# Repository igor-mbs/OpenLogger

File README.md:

# OpenLogger

<!--

"Halley's method"
=640x640
{width=320 height=240}
-->
<!-- <figure>

<figcaption>Halley's method</figcaption>
</figure> -->
<!--  -->
<!--  -->
<!--  -->
<!--  -->
<!--  -->
<!--  -->
<!-- {width=50 height=50} -->
<!-- {width=500px}
{width=50} -->
<!-- {width=50%} -->

## Introduction

&nbsp;&nbsp;&nbsp;&nbsp;This project is and Open-source portable datalogger based on the ATmega328p microcontroller.

&nbsp;&nbsp;&nbsp;&nbsp; The intent for this project is to provide an cost-friendly solution to support micro and small companies as well as the generall public. The project consists in an semi-modular data acquisition device capable of comunication with probes compatible with digital comunication, like I2C, SPI, serial and PWM.
Open-source portable datalogger project based on the ATmega328p microcontroller.

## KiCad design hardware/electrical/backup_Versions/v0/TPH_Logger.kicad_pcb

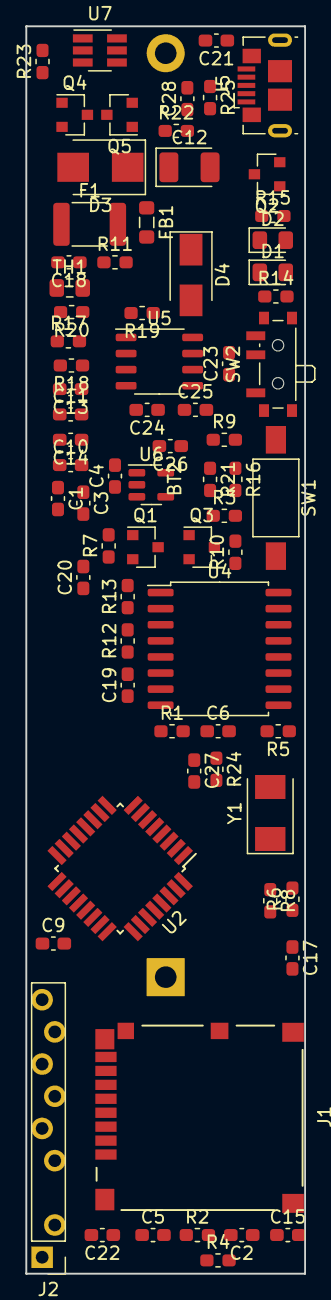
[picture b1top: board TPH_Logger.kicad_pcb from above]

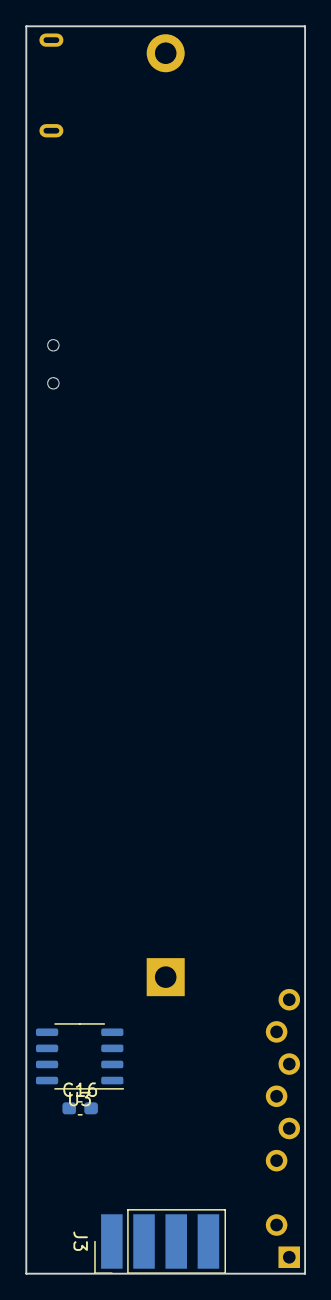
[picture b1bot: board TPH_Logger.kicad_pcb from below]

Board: 2 copper layers, 22.0 x 98.4 mm, 77 parts (3 on the bottom side), 44 nets, no tracks yet.

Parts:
BT2: 18650 Li-Ion (4.3-2.7V); 18650holder
C1, C9, C11, C13, C14, C28: 100n; C_0603_1608Metric_Pad1.08x0.95mm_HandSolder
C2, C3, C4, C5, C17, C18, C19, C20: 12p; C_0603_1608Metric_Pad1.08x0.95mm_HandSolder
C6, C21, C22: 1u; C_0603_1608Metric_Pad1.08x0.95mm_HandSolder
C10, C26: 10n; C_0603_1608Metric_Pad1.08x0.95mm_HandSolder
C12: 4.7u; CP_EIA-3528-21_Kemet-B_Pad1.50x2.35mm_HandSolder
C15, C16: 22p; C_0603_1608Metric_Pad1.08x0.95mm_HandSolder
C23, C27: 4.7u; C_0603_1608Metric_Pad1.08x0.95mm_HandSolder
C24, C25: 10u; C_0603_1608Metric_Pad1.08x0.95mm_HandSolder
D1, D2: LED; LED_0805_2012Metric_Pad1.15x1.40mm_HandSolder
D3: P6SMB6.8A; D_SMB
D4: MBRA340; D_SMA
F1: MF-MSMF050/30; R_1812_4532Metric_Pad1.30x3.40mm_HandSolder
FB1: CB05YTYH600-1; L_0805_2012Metric_Pad1.05x1.20mm_HandSolder
J1: Micro_SD_Card; molex-MicroSD-5027740891
J2: ICSP; Igor Prog
J3: External_I2C_0; my_i2c_smd
J5: USB_B_Mini; USB_Micro-B_GCT_USB3076-30-A
Q1, Q4, Q5: AO3400A; SOT-23
Q2, Q3: AO3401A; SOT-23
R1, R2, R3, R4, R10, R11, R12, R13: 3.3k; R_0603_1608Metric_Pad1.05x0.95mm_HandSolder
R5, R16, R25: 100k; R_0603_1608Metric_Pad1.05x0.95mm_HandSolder
R6, R24: 1k; R_0603_1608Metric_Pad1.05x0.95mm_HandSolder
R7, R9, R14, R15, R21: 10k; R_0603_1608Metric_Pad1.05x0.95mm_HandSolder
R8: 1K; R_0603_1608Metric_Pad1.05x0.95mm_HandSolder
R17: 2,2k; R_0603_1608Metric_Pad1.05x0.95mm_HandSolder
R18: 330; R_0603_1608Metric_Pad1.05x0.95mm_HandSolder
R19: 4.7k; R_0603_1608Metric_Pad1.05x0.95mm_HandSolder
R20: 82k; R_0603_1608Metric_Pad1.05x0.95mm_HandSolder
R22: 470; R_0603_1608Metric_Pad1.05x0.95mm_HandSolder
R23: 2K; R_0603_1608Metric_Pad1.05x0.95mm_HandSolder
SW1: SW_Push; SW_SPST_FSMSM
SW2: SW_SPDT; SW_SPDT_PCM12
TH1: 10k NTC; R_0805_2012Metric_Pad1.15x1.40mm_HandSolder
U2: ATmega328P-A; TQFP-32_7x7mm_P0.8mm
U3: M24C64; SO-8_3.9x4.9mm_P1.27mm
U4: DS3231; SOIC-16W_7.5x10.3mm_P1.27mm
U5: TP4056; SOP-8_3.9x4.9mm_P1.27mm
U6: LP2985-3.3; SOT-23-5
U7: DW01-P; SOT-23-6_Handsoldering
Y1: 8M; Crystal_SMD_Abracon_ABM3-2Pin_5.0x3.2mm

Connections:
32kHz: C20.1, R13.2, U2.9, U4.1
+3V3: C10.2, C11.2, C12.1, C13.1, C14.1, C27.1, J2.1, Q3.2, R12.2, R13.1, R21.1, U2.4, U2.6, U2.18, U4.2, U6.5
+18650: BT2.1, C25.2, C28.1, Q2.3, R22.2, U5.5
+USB: C22.2, C24.2, D4.2, F1.1, Q2.1, R14.1, R15.1, R19.1, R25.2, U5.4, U5.8
+VBus: C23.2, D4.1, Q2.2, SW2.3, U6.1
-18650: BT2.2, C28.2, Q5.2, R25.1, U7.6
-CR1220: C1.1, C2.1, C3.1, C4.1, C5.1, C6.1, C9.2, C10.1, C11.1, C12.2, C13.2, C14.2, C15.1, C16.1, C17.2, C18.2, C19.1, C20.2, C21.2, C22.1, C23.1, C24.1, C25.1, C26.2, C27.2, D3.2, J1.6, J2.4, J3.2, J5.5, Q1.2, Q4.2, R5.2, R7.1, R16.2, R18.2, R20.2, R23.1, SW1.2, SW2.1, TH1.1, U2.3, U2.5, U2.21, U3.1, U3.2, U3.4, U3.7, U4.5, U4.6, U4.7, U4.8, U4.9, U4.10, U4.11, U4.12, U4.13, U5.3, U6.2
CS_0: C5.2, J1.2, R4.1, U2.14
Log_supply: C1.2, J1.4, J3.1, Q3.3, R1.2, R2.2, R3.2, R4.2, R9.1, R10.2, R11.2, U3.8
Log_supply_control: R24.2, U2.10
MISO: C2.2, J1.7, J2.6, R1.1, U2.16
MOSI: C4.2, J1.3, J2.5, R3.1, U2.15
unnamed: C6.2, J1.9, R5.1
unnamed: C9.1, U2.20
unnamed: C15.2, U2.7, Y1.1
unnamed: C16.2, U2.8, Y1.2
unnamed: C21.1, J5.6, R16.1
unnamed: C26.1, U6.4
unnamed: D1.1, U5.6
unnamed: D1.2, R14.2
unnamed: D2.1, U5.7
unnamed: D2.2, R15.2
unnamed: D3.1, FB1.1, J5.1
unnamed: F1.2, FB1.2
unnamed: Q1.1, R7.2, R24.1
unnamed: Q1.3, Q3.1, R21.2
unnamed: Q4.1, U7.3
unnamed: Q4.3, Q5.3
unnamed: Q5.1, U7.1
unnamed: R6.1, U2.30
unnamed: R8.2, U2.31
unnamed: R17.1, U5.2
unnamed: R17.2, R18.1
unnamed: R19.2, R20.1, TH1.2, U5.1
unnamed: R22.1, U7.5
unnamed: R23.2, U7.2
unnamed: SW2.2, U6.3
RX: J2.2, R6.2
SCK: C3.2, J1.5, J2.7, R2.1, U2.17
SCL: C17.1, J3.3, R10.1, U2.28, U3.6, U4.16
SDA: C18.1, J3.4, R11.1, U2.27, U3.5, U4.15
TX: J2.3, R8.1
~INT~\SQW: C19.2, R12.1, U2.32, U4.3
~RESET: J2.8, R9.2, SW1.1, U2.29
